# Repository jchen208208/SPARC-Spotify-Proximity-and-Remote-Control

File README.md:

# 🎵 SPARC

**S**potify **P**roximity **a**nd **R**emote **C**ontrol — a desk-mounted gesture controller.
Wave your hand over it to skip tracks, change volume, or pause. No touchscreen, no buttons,
no phone.

Built for situations where looking at a screen is inconvenient or unsafe — adjusting music
while driving, mainly.

---

## How it works

SPARC pairs to your phone or laptop as a **Bluetooth media remote** — the same class of
device as the play/pause button on a pair of headphones.

It does not talk to Spotify. It sends standard HID media-key presses to the operating
system, which routes them to whatever app is currently playing. That means:

- **No app to install** — pair it in Bluetooth settings and it works
- **No Spotify account, login, or Premium subscription**
- Works on **iOS, Android, macOS, Windows, Linux**
- Works with **any** media app — Spotify, Apple Music, YouTube, podcasts

It also works with the screen off and the phone in your pocket, for the same reason your
headphone buttons do.

---

## Gestures

Two zones above the sensor:

| Zone | Range | Controls |
|---|---|---|
| 1 | 2–15 cm | Tracks |
| 2 | 15–30 cm | Volume |

| Gesture | Zone 1 | Zone 2 |
|---|---|---|
| Single pass | ⏭ Next track | 🔊 Volume up |
| Double pass (within 0.8s) | ⏮ Previous track | 🔉 Volume down |
| Hold (0.3s) | ⏯ Play/pause | ⏹ Stop the volume ramp |

Volume ramps continuously once started. Hold your hand still to stop it.

---

## Hardware

| Component | Notes |
|---|---|
| ESP32 (WROOM-32) | Built-in Bluetooth — no separate radio module |
| VL53L0X | Time-of-flight distance sensor, I²C on SDA 21 / SCL 22 |
| 8× WS2812B | Volume bar, data on GPIO 18 |
| LED | Play/pause flash, GPIO 4 |

Runs off a power bank.

---

## Flashing

Requires the ESP32 board core, plus the `NimBLE-Arduino`, `Adafruit_VL53L0X` and `FastLED`
libraries.

```bash
arduino-cli compile --fqbn esp32:esp32:esp32 --port /dev/cu.usbserial-0001 --upload sketch_esp_hid
```

Then pair "SPARC" from your device's Bluetooth settings. That's the whole setup.

> A BLE device stops advertising while connected. To pair it to something else, disconnect
> — or **forget** it — on the current device first, or it won't be discoverable.

---

## Repo layout

| Path | |
|---|---|
| `sketch_esp_hid/` | **The product.** BLE HID firmware |
| `sketch_esp/` | Older firmware that talks to the desktop app over Bluetooth Serial |
| `Main.py`, `ui.py`, `core.py` | Desktop app — demo only, see below |
| `Wired_version/`, `Uno_version/`, `sketch_nano/` | Earlier hardware revisions, kept for reference |

**The desktop app is a demo artifact, not part of the product.** It shows album art, a queue
wheel and gesture animations, but it needs the Spotify Web API — which is exactly the
limitation the HID firmware exists to escape. It only works with `sketch_esp/` firmware
flashed; the two builds are mutually exclusive.

---

## Project timeline

What we tried, what broke, and what we changed.

| Stage | Problem | Fix |
|---|---|---|
| **Proximity volume** | Mapping hand *distance* to volume was buggy and misread hand position constantly. Roughly a full day lost to it. | Scrapped continuous tracking for discrete swipes — single pass, double pass, hold. |
| **USB tether** | The board had to stay plugged into the laptop, so it wasn't really a remote. | Went wireless. Tried WiFi first, settled on Bluetooth with an HC-05. |
| **HC-05 on macOS** | Pairing and holding a stable serial connection took a lot of troubleshooting. | Worked through the port/pairing issues, then moved to an ESP32 — its built-in radio removed the separate module entirely. |
| **Terminal window** | The packaged executable still opened a terminal on launch. Not a product. | Built a proper macOS `.app` with a status UI and gesture animations. |
| **Spotify API cap** ⚠️ | Spotify cut Development Mode to **5 users** in Feb 2026 and required Premium. Extended quota has been organisations-only since May 2025 — no application path for us. **Hard ceiling on the entire product.** | Stopped using the API. Became a **BLE HID device** instead, so the OS routes the commands. Removed the user cap, the Premium requirement, and the app install in one change — and made iPhone possible for the first time, since iOS never supported the old Bluetooth Serial transport. |

### Along the way

- **Leaked credentials.** Early commits contained Spotify tokens. Moved to `.env`, gitignored, purged from history.
- **Sensor took the whole board down.** On a cold power-up the VL53L0X is still booting when `begin()` runs. Failing silently wedged `setup()`, so Bluetooth never came up and the board looked dead. Now it retries five times and carries on regardless.
- **The on-screen keyboard trap.** Off-the-shelf ESP32 HID libraries declare themselves as keyboards, which makes iOS hide the on-screen keyboard system-wide — you couldn't type in any app while SPARC was connected. Fixed by hand-writing a report descriptor that declares media keys *only*.

---

## What's next

- Solder onto perfboard, ditch the breadboard
- Build a case
- A pairing gesture, so switching between devices doesn't mean digging through Bluetooth settings

---

## License

MIT

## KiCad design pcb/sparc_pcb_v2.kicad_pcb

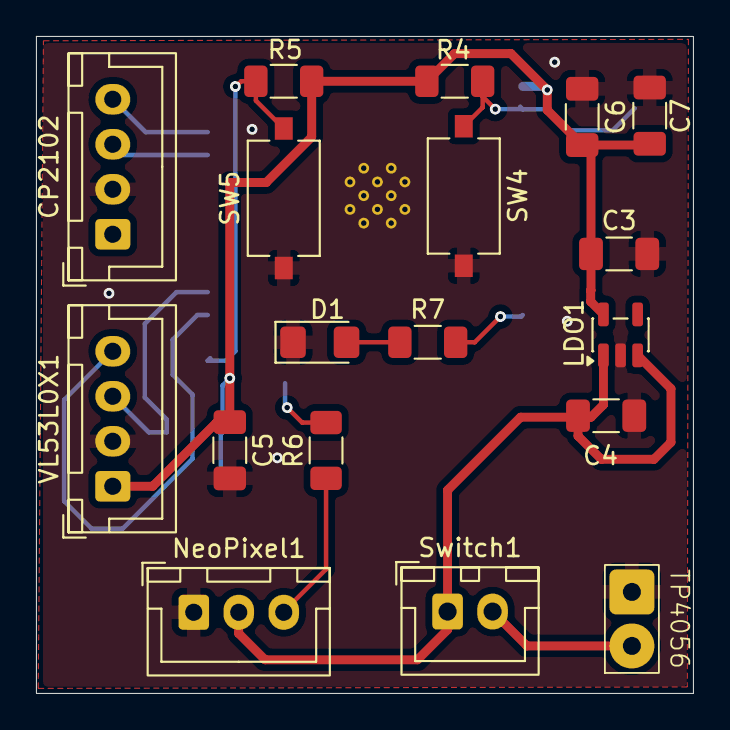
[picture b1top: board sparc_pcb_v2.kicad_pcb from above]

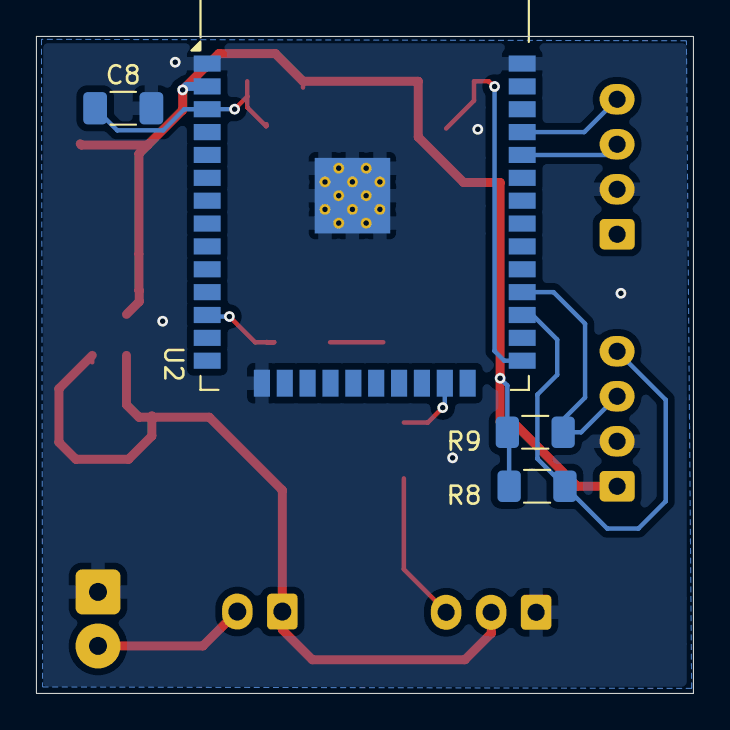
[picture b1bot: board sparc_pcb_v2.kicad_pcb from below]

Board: 2 copper layers, 36.5 x 36.5 mm, 22 parts (4 on the bottom side), 14 nets.

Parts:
C3, C4, C8: 1µF; C_1206_3216Metric_Pad1.33x1.80mm_HandSolder
C5, C6: 0.1µF; C_1206_3216Metric_Pad1.33x1.80mm_HandSolder
C7: 10µF; C_1206_3216Metric_Pad1.33x1.80mm_HandSolder
CP2102: JST_XH_B4B-XH-A_1x04_P2.50mm_Vertical
D1: LED; LED_1206_3216Metric_Pad1.42x1.75mm_HandSolder
LDO1: AP2112K-3.3; SOT-23-5
NeoPixel1: JST_XH_B3B-XH-A_1x03_P2.50mm_Vertical
R4, R5: 10k; R_1206_3216Metric_Pad1.30x1.75mm_HandSolder
R6, R7: 330; R_1206_3216Metric_Pad1.30x1.75mm_HandSolder
R8, R9: 4.7k; R_1206_3216Metric_Pad1.30x1.75mm_HandSolder
SW4: Reset; SW_Tactile_SPST_NO_Straight_CK_PTS636Sx25SMTRLFS
SW5: BOOT; SW_Tactile_SPST_NO_Straight_CK_PTS636Sx25SMTRLFS
Switch1: JST_XH_B2B-XH-A_1x02_P2.50mm_Vertical
TP4056: TP4056 OUT+_-
U2: ESP32-WROOM-32
VL53L0X1: JST_XH_B4B-XH-A_1x04_P2.50mm_Vertical

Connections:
+3.3V: C3.1, C5.1, C6.2, C7.1, LDO1.5 (VOUT), R4.2, R5.1, R8.1, R9.1, U2.2 (VDD), VL53L0X1.1 (+3V3)
GND: C3.2, C4.2, C5.2, C6.1, C7.2, C8.2, CP2102.2 (GND), D1.1 (K), LDO1.2 (GND), NeoPixel1.1 (GND), SW4.1, SW5.1, TP4056.4 (OUT-), U2.1 (GND), U2.15 (GND), U2.38 (GND), U2.39 (GND), VL53L0X1.2 (GND)
unnamed: CP2102.4 (RXD), U2.35 (TXD0/IO1)
unnamed: CP2102.3 (TXD), U2.34 (RXD0/IO3)
unnamed: D1.2 (A), R7.1
unnamed: NeoPixel1.3 (DIN), R6.1
unnamed: Switch1.2 (B), TP4056.1 (OUT+)
unnamed: C8.1, R4.1, SW4.2, U2.3 (EN)
unnamed: R5.2, SW5.2, U2.25 (IO0)
unnamed: R6.2, U2.23 (IO15)
unnamed: R8.2, U2.27 (IO16), VL53L0X1.4 (SDA)
unnamed: R9.2, U2.28 (IO17), VL53L0X1.3 (SCL)
unnamed: R7.2, U2.12 (IO27)
TP4056 OUT+: C4.1, LDO1.1 (VIN), LDO1.3 (EN), NeoPixel1.2 (+5V), Switch1.1 (A)

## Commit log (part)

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2026-06-16 README description
2026-06-16 Add MIT License to the project
2026-06-17 Main.py draft
2026-06-17 Main
2026-06-17 SPARC Logo
    Updated project name and added an image to README.
2026-06-17 resize
    Updated image size in README.md for better display.
2026-06-17 logo resize
    Updated image in README with a new screenshot.
2026-06-17 Adjust image size in README.md
    Updated image dimensions in README for better display.
2026-06-17 readme
2026-06-17 hopefully final update to sketch.ino
2026-06-18 added .gitignore
    if you want to put any files into the repo directory and don't want it to actually show up on the github repo, add it to the .gitignore file using echo "filename.filetype" >> .gitignore
2026-06-18 Test Mode While Loop
    since we haven't linked laptop up to uno yet.
2026-06-18 used a .env folder for private data
2026-06-18 toggle playback
    toggle the BIG playback
2026-06-18 2 second hold time
    Corrected the comment for HOLD_TIME to reflect the accurate duration.
2026-06-18 security fix
    conrad lee head of security
2026-06-18 serial signal rework
    I made it so that let's say the spotify app is at 60% when the user enters volume mode, we calculate the 0% adn 100% distances relative to the current distance, and then we can transfer that onto the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
2026-06-18 Main.py had an error
    swapperdMemoryCacheHandler and went back to SpotifyOAuth. Works now.
2026-06-18 Clean up comments in sketch.ino
    Removed unused gesture map comments from sketch.ino
2026-06-18 killed V_start
    murder
2026-06-18 no 2
    ye
2026-06-18 put the file in the folder
    file folder
2026-06-18 nvm i mess up its fix now
    ye
2026-06-18 pauses fix
    fix the pause
2026-06-18 connected uno input to python script
2026-06-18 pause fix again
    pause please fixed
2026-06-18 made python script display enter or exit swithc or volume mode
2026-06-18 new gesture system that ACTUALLY WORKS
    yay
2026-06-18 connected to main
2026-06-18 step: 7%, interval: 0.1s
2026-06-18 hello
    finish
2026-06-19 FIX THE VOLUME
    volume is FIXED
2026-06-19 BIG PUSH
    the biggest push
2026-06-19 os if else
    so we don't have to change serial ports manually
2026-06-19 big push
    yes
2026-06-19 mp3 files
2026-06-19 "connected" "disconnected" and then fix the restart/backtrack
2026-06-19 LED FINAL PULL FROM HERE IF EXPLOSION
    boom
2026-06-19 WiFi IMPLEMENTATION
    YEs
2026-06-19 Made copies for the wired version scripts
2026-06-19 new wired_version folder but with just the changed files
2026-06-19 wired working
2026-06-19 Remove .venv and .cache from version control, update .gitignore
2026-06-19 Remove cached Spotify tokens from Wired_version
2026-06-19 LED bug fixed for wired version
2026-06-19 WIRELESS
    wireless
2026-06-19 Apply .gitignore to untrack files
2026-06-20 driving
2026-06-22 LED turns off completely when program is disconnected
2026-06-23 BLUETOOTH WORKS!
    yay
2026-06-23 hel;o
    WORK
2026-06-23 fixing bluetooth issue
    got rid of the code that automatically exits the c++ program if the bluetooth isn't connected
